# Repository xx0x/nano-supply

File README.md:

# Nano Supply
Compact open source Eurorack USB-C power supply. Uses USB-PD and requires at least **9V**; should work with most USB-C *fast chargers* for phones and laptops.

Lights red on unsupported USB charger, and green when all is OK.

## Specs

- up to 1250 mA @ +12V
- up to 1250 mA @ -12V
- up to 600 mA @ +5V
  
## How it looks? 

## Schematics

## How to get it?

You can find gerber/BOM/CPL files inside `pcb/nano-supply-v2b/jlcpcb/production_files`, the Nano Supply is not available for purchase neither as a kit or built unit at the moment.

## License

CERN-OHL-P-2.0

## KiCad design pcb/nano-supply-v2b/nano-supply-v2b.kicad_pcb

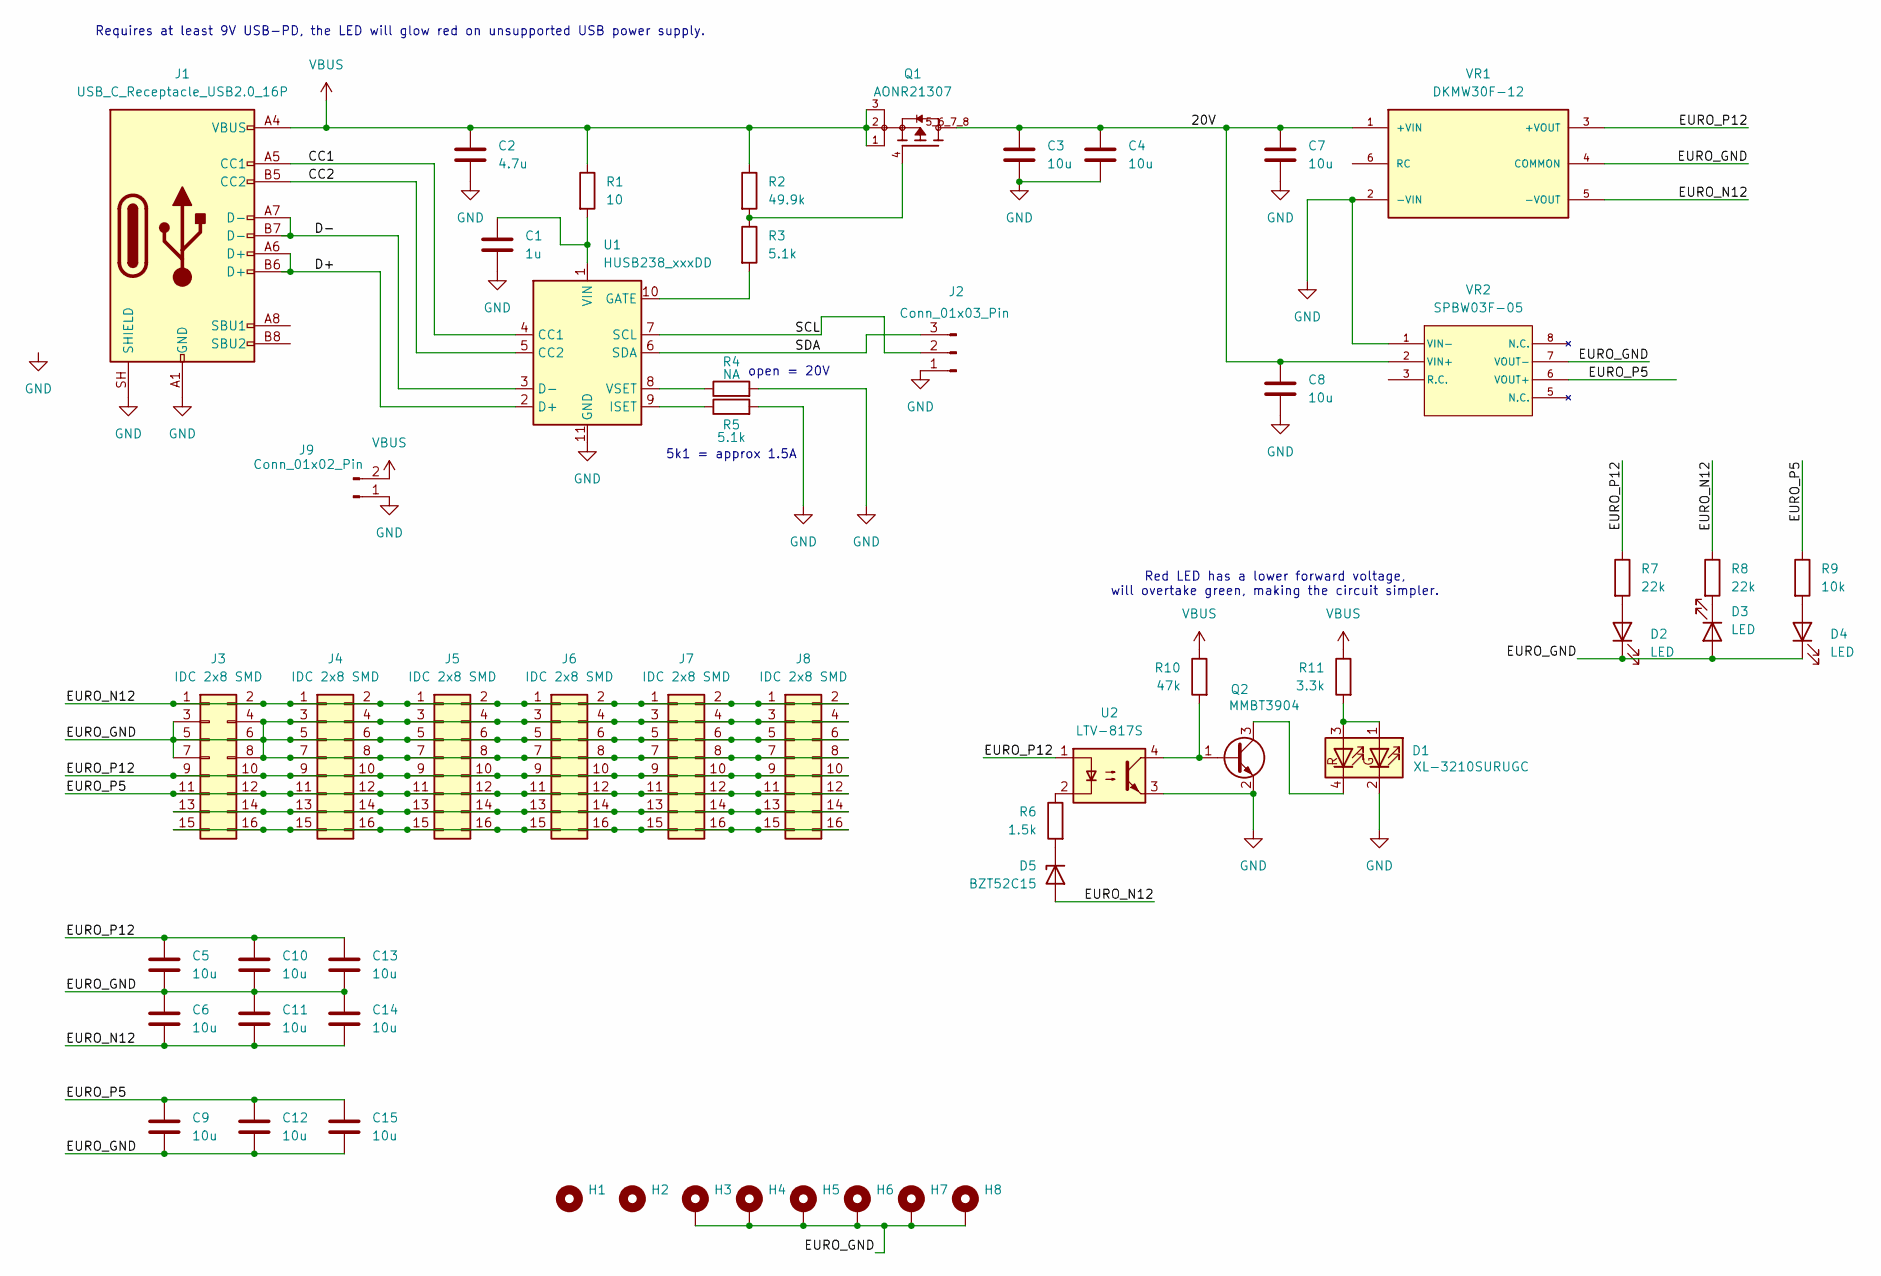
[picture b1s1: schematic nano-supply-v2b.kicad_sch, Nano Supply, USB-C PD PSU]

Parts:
C1: 1u; C_0603_1608Metric; LCSC C15849
C2: 4.7u; C_1206_3216Metric; LCSC C15850
C3, C4, C5, C6, C7, C8, C9, C10, C11, C12, C13, C14, C15: 10u; C_1206_3216Metric; LCSC C15850
D1: XL-3210SURUGC
D2, D3, D4: LED; LED_0603_1608Metric; LCSC C2290
D5: BZT52C15; D_SOD-123
H1, H2: MountingHole; MountingHole_3.2mm_M3
H3, H4, H5, H6, H7, H8: MountingHole_Pad; MountingHole_3.2mm_M3_Pad
J1: USB_C_Receptacle_USB2.0_16P; TYPE-C-31-M-12; LCSC C165948
J2: Conn_01x03_Pin; TestPads_1x03_P2.54mm
J3, J4, J5, J6, J7, J8: IDC 2x8 SMD; IDC-Header_2x08_P2.54mm_Vertical_SMD; LCSC C41376031
J9: Conn_01x02_Pin; TestPads_1x02_P2.54mm
Q1: AONR21307; TRANS_AONR21307; LCSC C3277813
Q2: MMBT3904; SOT-23
R1: 10; R_0603_1608Metric; LCSC C22859
R2: 49.9k; R_0603_1608Metric; LCSC C23184
R3, R5: 5.1k; R_0603_1608Metric; LCSC C23186
R4: NA; R_0603_1608Metric
R6: 1.5k; R_0805_2012Metric; LCSC C23186
R7, R8: 22k; R_0603_1608Metric; LCSC C31850
R9: 10k; R_0603_1608Metric; LCSC C31850
R10: 47k; R_0603_1608Metric; LCSC C23186
R11: 3.3k; R_0805_2012Metric; LCSC C23186
U1: HUSB238_xxxDD; WDFN-10-1EP_3x3mm_P0.5mm_EP1.8x2.5mm; LCSC C7471904
U2: LTV-817S; SMDIP-4_W9.53mm
VR1: DKMW30F-12; CONV_DKMW30F-12
VR2: SPBW03F-05; SPBW03F-05_MWU

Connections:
/20V: C3.1, C4.1, C7.1, C8.1, Q1.5_6_7_8, VR1.1 (+VIN), VR2.2 (VIN+)
/CC1: J1.A5 (CC1), U1.4 (CC1)
/CC2: J1.B5 (CC2), U1.5 (CC2)
/D+: J1.A6 (D+), J1.B6 (D+), U1.2 (D+)
/D-: J1.A7 (D-), J1.B7 (D-), U1.3 (D-)
/EURO_GND: C5.2, C6.1, C9.2, C10.2, C11.1, C12.2, C13.2, C14.1, C15.2, D2.1 (K), D3.2 (A), D4.1 (K), H3.1 (1_1), H4.1 (1_1), H5.1 (1_1), H6.1 (1_1), H7.1 (1_1), H8.1 (1_1), J3.3, J3.4, J3.5, J3.6, J3.7, J3.8, J4.3, J4.4, J4.5, J4.6, J4.7, J4.8, J5.3, J5.4, J5.5, J5.6, J5.7, J5.8, J6.3, J6.4, J6.5, J6.6, J6.7, J6.8, J7.3, J7.4, J7.5, J7.6, J7.7, J7.8, J8.3, J8.4, J8.5, J8.6, J8.7, J8.8, VR1.4 (COMMON), VR2.7 (VOUT-)
/EURO_N12: C6.2, C11.2, C14.2, D5.2 (A), J3.1, J3.2, J4.1, J4.2, J5.1, J5.2, J6.1, J6.2, J7.1, J7.2, J8.1, J8.2, R8.1, VR1.5 (-VOUT)
/EURO_P5: C9.1, C12.1, C15.1, J3.11, J3.12, J4.11, J4.12, J5.11, J5.12, J6.11, J6.12, J7.11, J7.12, J8.11, J8.12, R9.1, VR2.6 (VOUT+)
/EURO_P12: C5.1, C10.1, C13.1, J3.9, J3.10, J4.9, J4.10, J5.9, J5.10, J6.9, J6.10, J7.9, J7.10, J8.9, J8.10, R7.1, U2.1, VR1.3 (+VOUT)
/SCL: J2.2, U1.7 (SCL)
/SDA: J2.3, U1.6 (SDA)
GND: C1.2, C2.2, C3.2, C4.2, C7.2, C8.2, D1.2 (GK), J1.A1 (GND), J1.A12 (GND), J1.B1 (GND), J1.B12 (GND), J1.SH (SHIELD), J2.1, J9.1, Q2.2 (E), R4.2, R5.2, U1.11 (GND), U2.3, VR1.2 (-VIN), VR2.1 (VIN-)
unnamed: D1.1 (GA), D1.3 (RA), R11.2
unnamed: D1.4 (RK), Q2.3 (C)
unnamed: D2.2 (A), R7.2
unnamed: D3.1 (K), R8.2
unnamed: D4.2 (A), R9.2
unnamed: D5.1 (K), R6.2
unnamed: J3.13, J3.14, J4.13, J4.14, J5.13, J5.14, J6.13, J6.14, J7.13, J7.14, J8.13, J8.14
unnamed: J3.15, J3.16, J4.15, J4.16, J5.15, J5.16, J6.15, J6.16, J7.15, J7.16, J8.15, J8.16
unnamed: Q1.4, R2.2, R3.1
unnamed: Q2.1 (B), R10.2, U2.4
unnamed: R6.1, U2.2
unnamed: R3.2, U1.10 (GATE)
unnamed: R5.1, U1.9 (ISET)
unnamed: C1.1, R1.2, U1.1 (VIN)
unnamed: R4.1, U1.8 (VSET)
VBUS: C2.1, J1.A4 (VBUS), J1.A9 (VBUS), J1.B4 (VBUS), J1.B9 (VBUS), J9.2, Q1.1, Q1.2, Q1.3, R1.1, R2.1, R10.1, R11.1

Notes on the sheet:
5k1 = approx 1.5A
open = 20V
Red LED has a lower forward voltage, will overtake green, making the circuit simpler.
Requires at least 9V USB-PD, the LED will glow red on unsupported USB power supply.

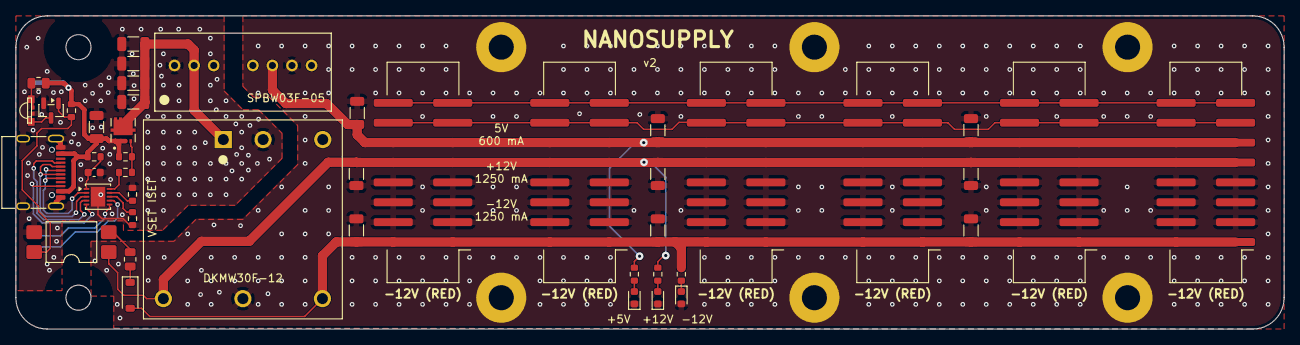
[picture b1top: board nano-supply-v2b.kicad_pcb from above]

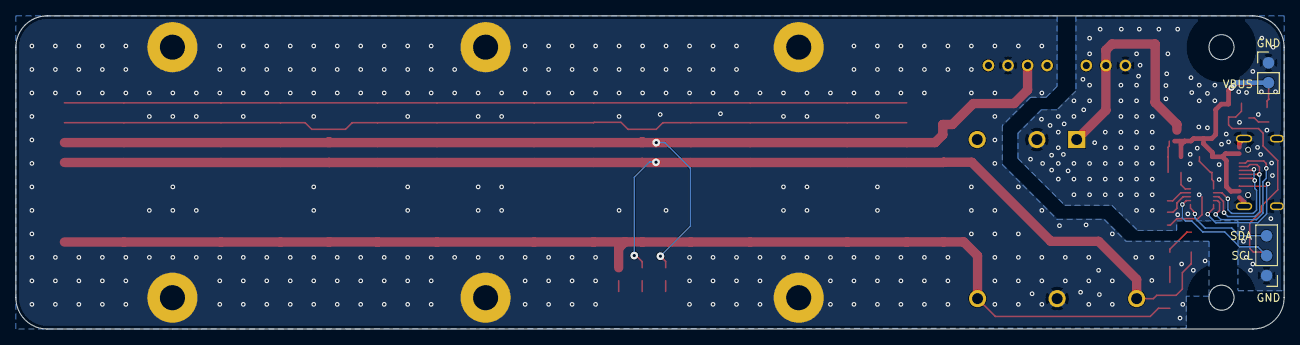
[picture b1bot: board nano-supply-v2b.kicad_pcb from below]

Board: 2 copper layers, 162.0 x 40.0 mm, 54 parts (2 on the bottom side), 28 nets.

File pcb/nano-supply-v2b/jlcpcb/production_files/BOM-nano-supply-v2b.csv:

Comment,Designator,Footprint,LCSC,Quantity
1.5k,R6,R_0805_2012Metric,C4310,1
10,R1,R_0603_1608Metric,C22859,1
10k,R9,R_0603_1608Metric,C25804,1
10u,"C10,C11,C12,C13,C14,C15,C3,C4,C5,C6,C7,C8,C9",C_1206_3216Metric,C13585,13
1u,C1,C_0603_1608Metric,C15849,1
22k,"R7,R8",R_0603_1608Metric,C31850,2
3.3k,R11,R_0805_2012Metric,C26010,1
4.7u,C2,C_1206_3216Metric,C29823,1
47k,R10,R_0603_1608Metric,C25819,1
49.9k,R2,R_0603_1608Metric,C23184,1
5.1k,"R3,R5",R_0603_1608Metric,C23186,2
AONR21307,Q1,TRANS_AONR21307,C3277813,1
BZT52C15,D5,D_SOD-123,C19077412,1
HUSB238_xxxDD,U1,WDFN-10-1EP_3x3mm_P0.5mm_EP1.8x2.5mm,C7471904,1
IDC 2x8 SMD,"J3,J4,J5,J6,J7,J8",IDC-Header_2x08_P2.54mm_Vertical_SMD,C41376031,6
LED,"D2,D3,D4",LED_0603_1608Metric,C2290,3
LTV-817S,U2,SMDIP-4_W9.53mm,C109227,1
MMBT3904,Q2,SOT-23,C20526,1
USB_C_Receptacle_USB2.0_16P,J1,TYPE-C-31-M-12,C165948,1
XL-3210SURUGC,D1,XL-3210SURUGC,C965883,1
DKMW30F-12,VR1,CONV_DKMW30F-12,,1
Conn_01x03_Pin,J2,TestPads_1x03_P2.54mm,,1
SPBW03F-05,VR2,SPBW03F-05_MWU,,1
Conn_01x02_Pin,J9,TestPads_1x02_P2.54mm,,1
NA,R4,R_0603_1608Metric,,1

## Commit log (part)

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2025-12-12 schematics, board layout
2025-12-14 routing
2025-12-14 stitching vias, routing tweaks
2025-12-14 add jlc mappings etc
2025-12-14 bom, gerber updates
2026-01-05 add 3d stuff (spbw03f footprint is incorrect??)
2026-01-09 indication simulation, datasheets
